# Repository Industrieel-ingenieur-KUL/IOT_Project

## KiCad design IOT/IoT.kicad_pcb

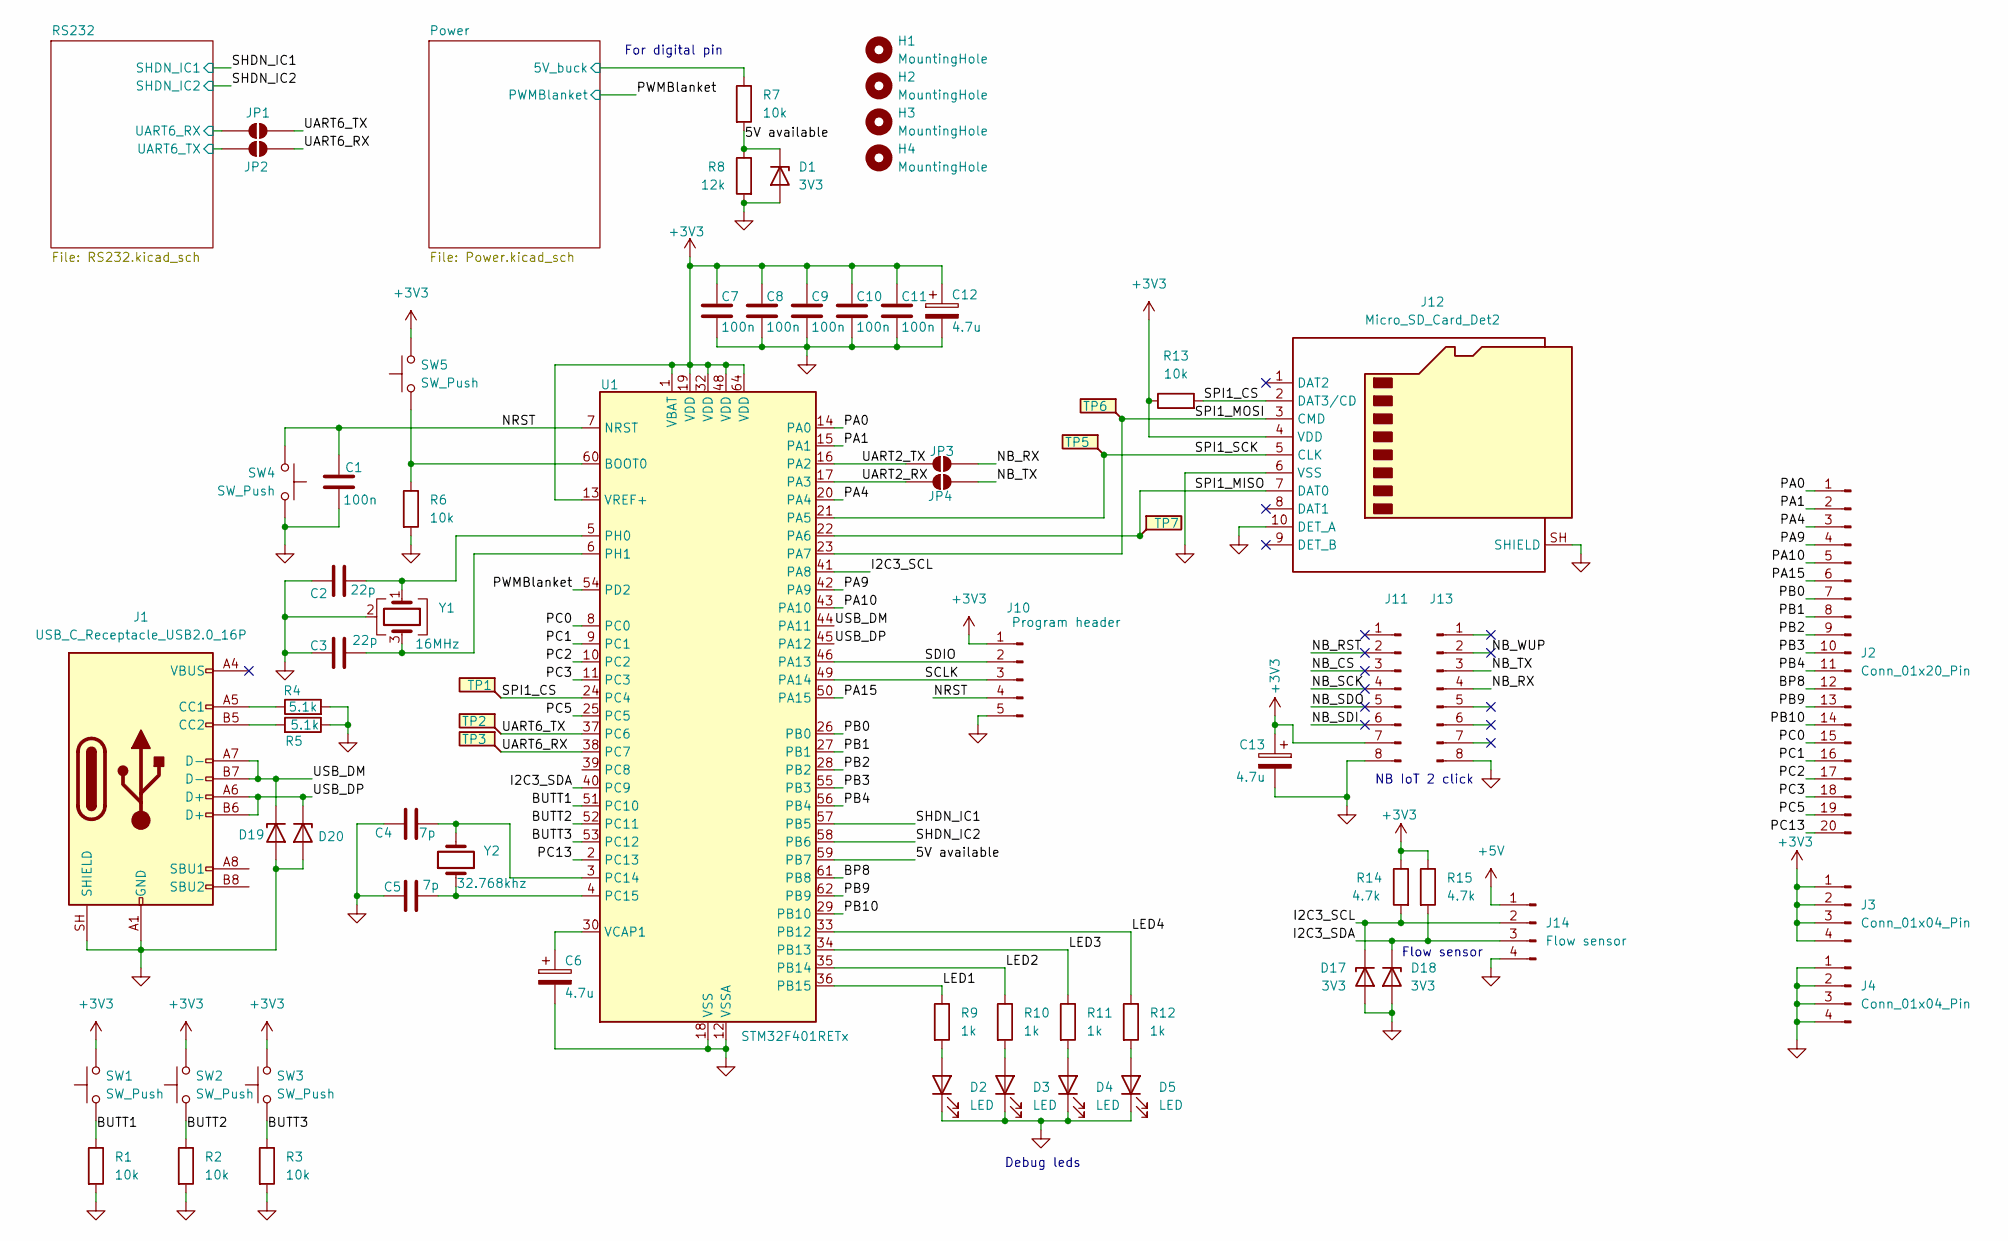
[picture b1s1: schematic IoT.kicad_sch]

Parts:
C1, C7, C8, C9, C10, C11: 100n; C_0805_2012Metric_Pad1.18x1.45mm_HandSolder
C2, C3: 22p; C_0805_2012Metric_Pad1.18x1.45mm_HandSolder
C4, C5: 7p; C_0805_2012Metric_Pad1.18x1.45mm_HandSolder
C6, C12, C13: 4.7u; C_0805_2012Metric_Pad1.18x1.45mm_HandSolder
D1, D17, D18: 3V3; Nexperia_CFP3_SOD-123W
D2, D3, D4, D5: LED; D_0805_2012Metric_Pad1.15x1.40mm_HandSolder
D19, D20: PTVS5V0Z1USK; D_1206_3216Metric_Pad1.42x1.75mm_HandSolder
H1, H2, H3, H4: MountingHole; MountingHole_5.3mm_M5_ISO14580
J1: USB_C_Receptacle_USB2.0_16P; USB_C_Receptacle_G-Switch_GT-USB-7010ASV
J2: Conn_01x20_Pin; PinHeader_1x20_P2.54mm_Vertical
J3, J4: Conn_01x04_Pin; PinSocket_1x04_P2.54mm_Vertical
J10: Program header; PinSocket_1x05_P2.54mm_Vertical
J11, J13: Conn_01x08_Pin; PinSocket_1x08_P2.54mm_Vertical
J12: Micro_SD_Card_Det2; microSD_HC_Molex_104031-0811
J14: Flow sensor; PinSocket_1x04_P2.54mm_Vertical
JP1, JP2, JP3, JP4: SolderJumper_2_Open; SolderJumper-2_P1.3mm_Open_RoundedPad1.0x1.5mm
R1, R2, R3, R6, R7, R13: 10k; LED_1206_3216Metric_Pad1.42x1.75mm_HandSolder
R4, R5: 5.1k; LED_1206_3216Metric_Pad1.42x1.75mm_HandSolder
R8: 12k; LED_1206_3216Metric_Pad1.42x1.75mm_HandSolder
R9, R10, R11, R12: 1k; LED_1206_3216Metric_Pad1.42x1.75mm_HandSolder
R14, R15: 4.7k; LED_1206_3216Metric_Pad1.42x1.75mm_HandSolder
SW1, SW2, SW3, SW4, SW5: SW_Push; SW_DIP_SPSTx01_Slide_6.7x4.1mm_W6.73mm_P2.54mm_LowProfile_J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
TP1, TP2, TP3, TP5, TP6, TP7: TestPoint_Flag; Pin_D0.7mm_L6.5mm_W1.8mm_FlatFork
U1: STM32F401RETx; LQFP-64_10x10mm_P0.5mm
Y1: 16MHz; Crystal_SMD_Abracon_ABM8AIG-4Pin_3.2x2.5mm
Y2: 32.768khz; Crystal_SMD_3215-2Pin_3.2x1.5mm

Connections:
+3V3: C7.1, C8.1, C9.1, C10.1, C11.1, C12.1, C13.1, J3.1, J3.2, J3.3, J3.4, J10.1, J11.7, J12.4 (VDD), R13.1, R14.1, R15.1, SW1.2, SW2.2, SW3.2, SW5.2, U1.1 (VBAT), U1.13 (VREF+), U1.19 (VDD), U1.32 (VDD), U1.48 (VDD), U1.64 (VDD); also elsewhere on the board
+5V: J14.1; also elsewhere on the board
/5V available: D1.1 (K), R7.2, R8.1, U1.59 (PB7)
/BP8: J2.12, U1.61 (PB8)
/BUTT1: R1.1, SW1.1, U1.51 (PC10)
/BUTT2: R2.1, SW2.1, U1.52 (PC11)
/BUTT3: R3.1, SW3.1, U1.53 (PC12)
/I2C3_SCL: D17.1 (K), J14.2, R14.2, U1.41 (PA8)
/I2C3_SDA: D18.1 (K), J14.3, R15.2, U1.40 (PC9)
/LED1: R9.1, U1.36 (PB15)
/LED2: R10.1, U1.35 (PB14)
/LED3: R11.1, U1.34 (PB13)
/LED4: R12.1, U1.33 (PB12)
/NB_CS: J11.3
/NB_RST: J11.2
/NB_RX: J13.4, JP3.2 (B)
/NB_SCK: J11.4
/NB_SDI: J11.6
/NB_SDO: J11.5
/NB_TX: J13.3, JP4.2 (B)
/NB_WUP: J13.2
/NRST: C1.1, J10.4, SW4.2, U1.7 (NRST)
/PA0: J2.1, U1.14 (PA0)
/PA1: J2.2, U1.15 (PA1)
/PA4: J2.3, U1.20 (PA4)
/PA9: J2.4, U1.42 (PA9)
/PA10: J2.5, U1.43 (PA10)
/PA15: J2.6, U1.50 (PA15)
/PB0: J2.7, U1.26 (PB0)
/PB1: J2.8, U1.27 (PB1)
/PB2: J2.9, U1.28 (PB2)
/PB3: J2.10, U1.55 (PB3)
/PB4: J2.11, U1.56 (PB4)
/PB9: J2.13, U1.62 (PB9)
/PB10: J2.14, U1.29 (PB10)
/PC0: J2.15, U1.8 (PC0)
/PC1: J2.16, U1.9 (PC1)
/PC2: J2.17, U1.10 (PC2)
/PC3: J2.18, U1.11 (PC3)
/PC5: J2.19, U1.25 (PC5)
/PC13: J2.20, U1.2 (PC13)
/PWMBlanket: U1.54 (PD2); also elsewhere on the board
/Power/5V_Buck: R7.1; also elsewhere on the board
/RS232/UART6_RX: JP1.1 (A); also elsewhere on the board
/RS232/UART6_TX: JP2.1 (A); also elsewhere on the board
/SCLK: J10.3, U1.49 (PA14)
/SDIO: J10.2, U1.46 (PA13)
/SHDN_IC1: U1.57 (PB5); also elsewhere on the board
/SHDN_IC2: U1.58 (PB6); also elsewhere on the board
/SPI1_CS: J12.2 (DAT3/CD), R13.2, TP1.1 (1_1), U1.24 (PC4)
/SPI1_MISO: J12.7 (DAT0), TP7.1 (1_1), U1.22 (PA6)
/SPI1_MOSI: J12.3 (CMD), TP6.1 (1_1), U1.23 (PA7)
/SPI1_SCK: J12.5 (CLK), TP5.1 (1_1), U1.21 (PA5)
/UART2_RX: JP4.1 (A), U1.17 (PA3)
/UART2_TX: JP3.1 (A), U1.16 (PA2)
/UART6_RX: JP2.2 (B), TP3.1 (1_1), U1.38 (PC7)
/UART6_TX: JP1.2 (B), TP2.1 (1_1), U1.37 (PC6)
/USB_DM: D19.1 (K), J1.A7 (D-), J1.B7 (D-), U1.44 (PA11)
/USB_DP: D20.1 (K), J1.A6 (D+), J1.B6 (D+), U1.45 (PA12)
GND: C1.2, C2.1, C3.1, C4.1, C5.1, C6.2, C7.2, C8.2, C9.2, C10.2, C11.2, C12.2, C13.2, D1.2 (A), D2.1 (K), D3.1 (K), D4.1 (K), D5.1 (K), D17.2 (A), D18.2 (A), D19.2 (A), D20.2 (A), J1.A1 (GND), J1.A12 (GND), J1.B1 (GND), J1.B12 (GND), J1.SH (SHIELD), J4.1, J4.2, J4.3, J4.4, J10.5, J11.8, J12.6 (VSS), J12.10 (DET_A), J12.SH (SHIELD), J13.8, J14.4, R1.2, R2.2, R3.2, R4.2, R5.1, R6.2, R8.2, SW4.1, U1.12 (VSSA), U1.18 (VSS), U1.31 (VSS), U1.47 (VSS), U1.63 (VSS), Y1.2 (G), Y1.4 (G); also elsewhere on the board
unnamed: D2.2 (A), R9.2
unnamed: D3.2 (A), R10.2
unnamed: D4.2 (A), R11.2
unnamed: D5.2 (A), R12.2
unnamed: J1.A5 (CC1), R4.1
unnamed: J1.B5 (CC2), R5.2
unnamed: R6.1, SW5.1, U1.60 (BOOT0)
unnamed: C4.2, U1.3 (PC14), Y2.2
unnamed: C5.2, U1.4 (PC15), Y2.1
unnamed: C2.2, U1.5 (PH0), Y1.1
unnamed: C3.2, U1.6 (PH1), Y1.3
unnamed: C6.1, U1.30 (VCAP1)

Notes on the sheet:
Debug leds
For digital pin
Flow sensor
NB IoT 2 click

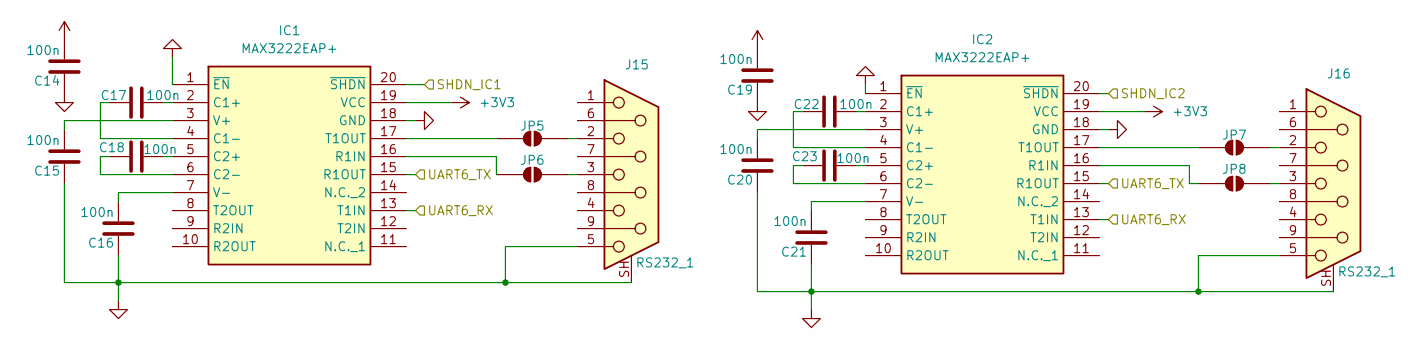
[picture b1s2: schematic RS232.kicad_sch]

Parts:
C14, C15, C16, C17, C18, C19, C20, C21, C22, C23: 100n; C_0805_2012Metric_Pad1.18x1.45mm_HandSolder
IC1, IC2: MAX3222EAP+; TSSOP-20_4.4x5mm_P0.4mm; Mouser Part Number 700-MAX3222EAP
J15, J16: RS232_1; DSUB-9_Pins_Horizontal_P2.77x2.84mm_EdgePinOffset14.56mm_Ho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
JP5, JP6, JP7, JP8: SolderJumper_2_Open; SolderJumper-2_P1.3mm_Open_RoundedPad1.0x1.5mm

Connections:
+3V3: C14.2, C19.2, IC1.19 (VCC), IC2.19 (VCC); also elsewhere on the board
/RS232/UART6_RX: IC1.13 (T1IN), IC2.13 (T1IN); also elsewhere on the board
/RS232/UART6_TX: IC1.15 (R1OUT), IC2.15 (R1OUT); also elsewhere on the board
/SHDN_IC1: IC1.20 (~SHDN); also elsewhere on the board
/SHDN_IC2: IC2.20 (~SHDN); also elsewhere on the board
GND: C14.1, C15.1, C16.1, C19.1, C20.1, C21.1, IC1.1 (~EN), IC1.18 (GND), IC2.1 (~EN), IC2.18 (GND), J15.5, J15.SH (PAD), J16.5, J16.SH (PAD); also elsewhere on the board
unnamed: C17.2, IC1.2 (C1+)
unnamed: C17.1, IC1.4 (C1-)
unnamed: C18.2, IC1.5 (C2+)
unnamed: C18.1, IC1.6 (C2-)
unnamed: IC1.16 (R1IN), JP6.1 (A)
unnamed: IC1.17 (T1OUT), JP5.1 (A)
unnamed: C15.2, IC1.3 (V+)
unnamed: C16.2, IC1.7 (V-)
unnamed: C22.2, IC2.2 (C1+)
unnamed: C22.1, IC2.4 (C1-)
unnamed: C23.2, IC2.5 (C2+)
unnamed: C23.1, IC2.6 (C2-)
unnamed: IC2.16 (R1IN), JP8.1 (A)
unnamed: IC2.17 (T1OUT), JP7.1 (A)
unnamed: C20.2, IC2.3 (V+)
unnamed: C21.2, IC2.7 (V-)
unnamed: J15.2, JP5.2 (B)
unnamed: J15.3, JP6.2 (B)
unnamed: J16.2, JP7.2 (B)
unnamed: J16.3, JP8.2 (B)

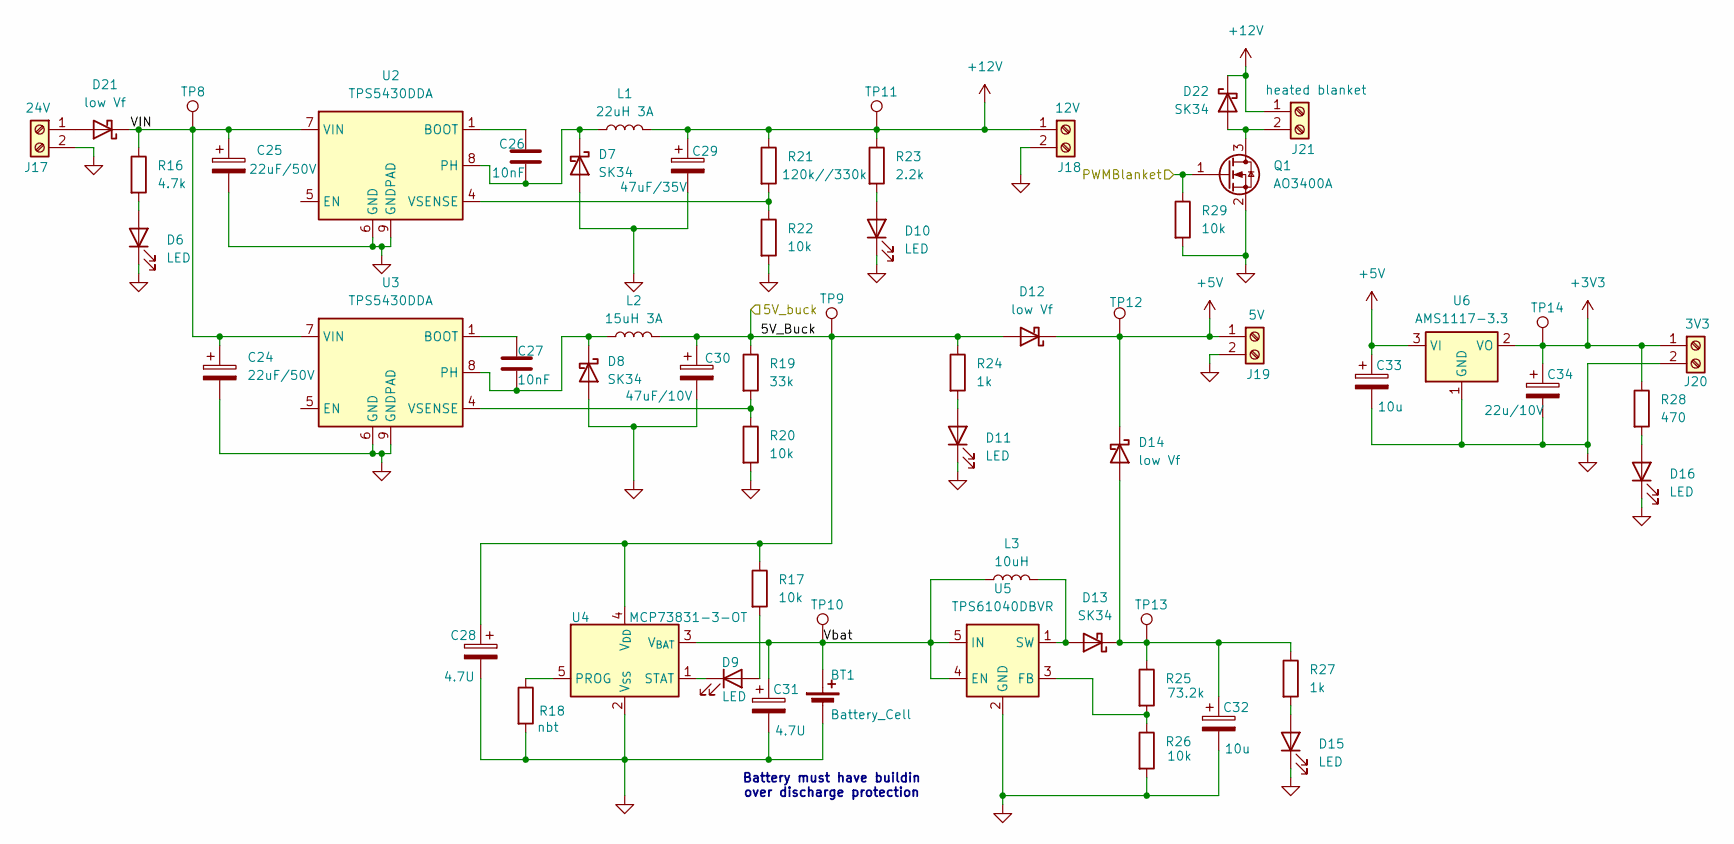
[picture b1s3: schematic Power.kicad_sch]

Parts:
BT1: Battery_Cell; BatteryHolder_MPD_BH-18650-PC
C24, C25: 22uF/50V; CP_Elec_5x5.4
C26, C27: 10nF; C_0805_2012Metric_Pad1.18x1.45mm_HandSolder
C28, C31: 4.7U; CP_Elec_4x5.4
C29: 47uF/35V; CP_Elec_8x10
C30: 47uF/10V; CP_Elec_8x10
C32, C33: 10u; C_0805_2012Metric_Pad1.18x1.45mm_HandSolder
C34: 22u/10V; CP_EIA-3528-12_Kemet-T_HandSolder
D6, D9, D10, D11, D15, D16: LED; D_0805_2012Metric_Pad1.15x1.40mm_HandSolder
D7, D8, D13, D22: SK34; D_SMA_Handsoldering
D12, D14, D21: low Vf; D_SMC_Handsoldering
J17: 24V; TerminalBlock_Philmore_TB132_1x02_P5.00mm_Horizontal
J18: 12V; TerminalBlock_Philmore_TB132_1x02_P5.00mm_Horizontal
J19: 5V; TerminalBlock_Philmore_TB132_1x02_P5.00mm_Horizontal
J20: 3V3; TerminalBlock_Philmore_TB132_1x02_P5.00mm_Horizontal
J21: heated blanket; TerminalBlock_Philmore_TB132_1x02_P5.00mm_Horizontal
L1: 22uH 3A; L_Wuerth_WE-PD-Typ-LS_Handsoldering
L2: 15uH 3A; L_Bourns_SRP7028A_7.3x6.6mm
L3: 10uH; L_Bourns_SRP7028A_7.3x6.6mm
Q1: AO3400A; SOT-23
R16: 4.7k; LED_1206_3216Metric_Pad1.42x1.75mm_HandSolder
R17, R20, R22, R26, R29: 10k; LED_1206_3216Metric_Pad1.42x1.75mm_HandSolder
R18: nbt; LED_1206_3216Metric_Pad1.42x1.75mm_HandSolder
R19: 33k; LED_1206_3216Metric_Pad1.42x1.75mm_HandSolder
R21: 120k//330k; LED_1206_3216Metric_Pad1.42x1.75mm_HandSolder
R23: 2.2k; LED_1206_3216Metric_Pad1.42x1.75mm_HandSolder
R24, R27: 1k; LED_1206_3216Metric_Pad1.42x1.75mm_HandSolder
R25: 73.2k; LED_1206_3216Metric_Pad1.42x1.75mm_HandSolder
R28: 470; LED_1206_3216Metric_Pad1.42x1.75mm_HandSolder
TP8, TP9, TP10, TP11, TP12, TP13, TP14: TestPoint; Pin_D0.7mm_L6.5mm_W1.8mm_FlatFork
U2, U3: TPS5430DDA; TI_SO-PowerPAD-8_ThermalVias
U4: MCP73831-3-OT; SOT-23-5
U5: TPS61040DBVR; SOT-23-6
U6: AMS1117-3.3; SOT-223-3_TabPin2

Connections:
+3V3: C34.1, J20.1, R28.1, TP14.1 (1_1), U6.2 (VO); also elsewhere on the board
+5V: C33.1, D12.1 (K), D14.1 (K), J19.1, TP12.1 (1_1), U6.3 (VI); also elsewhere on the board
+12V: C29.1, D22.1 (K), J18.1, J21.1, L1.2, R21.1, R23.1, TP11.1 (1_1)
/PWMBlanket: Q1.1 (G), R29.1; also elsewhere on the board
/Power/5V_Buck: C28.1, C30.1, D12.2 (A), L2.2, R17.1, R19.1, R24.1, TP9.1 (1_1), U4.4 (V_{DD}); also elsewhere on the board
/Power/VIN: C24.1, C25.1, D21.1 (K), R16.1, TP8.1 (1_1), U2.7 (VIN), U3.7 (VIN)
/Power/Vbat: BT1.1 (+), C31.1, L3.1, TP10.1 (1_1), U4.3 (V_{BAT}), U5.4 (EN), U5.5 (IN)
GND: BT1.2 (-), C24.2, C25.2, C28.2, C29.2, C30.2, C31.2, C32.2, C33.2, C34.2, D6.1 (K), D7.2 (A), D8.2 (A), D10.1 (K), D11.1 (K), D15.1 (K), D16.1 (K), J17.2, J18.2, J19.2, J20.2, Q1.2 (S), R18.2, R20.2, R22.2, R26.2, R29.2, U2.6 (GND), U2.9 (GNDPAD), U3.6 (GND), U3.9 (GNDPAD), U4.2 (V_{SS}), U5.2 (GND), U6.1 (GND); also elsewhere on the board
unnamed: D6.2 (A), R16.2
unnamed: C26.2, D7.1 (K), L1.1, U2.8 (PH)
unnamed: C27.2, D8.1 (K), L2.1, U3.8 (PH)
unnamed: D9.2 (A), R17.2
unnamed: D9.1 (K), U4.1 (STAT)
unnamed: D10.2 (A), R23.2
unnamed: D11.2 (A), R24.2
unnamed: D13.2 (A), L3.2, U5.1 (SW)
unnamed: C32.1, D13.1 (K), D14.2 (A), R25.1, R27.1, TP13.1 (1_1)
unnamed: D15.2 (A), R27.2
unnamed: D16.2 (A), R28.2
unnamed: D21.2 (A), J17.1
unnamed: D22.2 (A), J21.2, Q1.3 (D)
unnamed: C26.1, U2.1 (BOOT)
unnamed: R21.2, R22.1, U2.4 (VSENSE)
unnamed: C27.1, U3.1 (BOOT)
unnamed: R19.2, R20.1, U3.4 (VSENSE)
unnamed: R18.1, U4.5 (PROG)
unnamed: R25.2, R26.1, U5.3 (FB)

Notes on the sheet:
Battery must have buildin over discharge protection

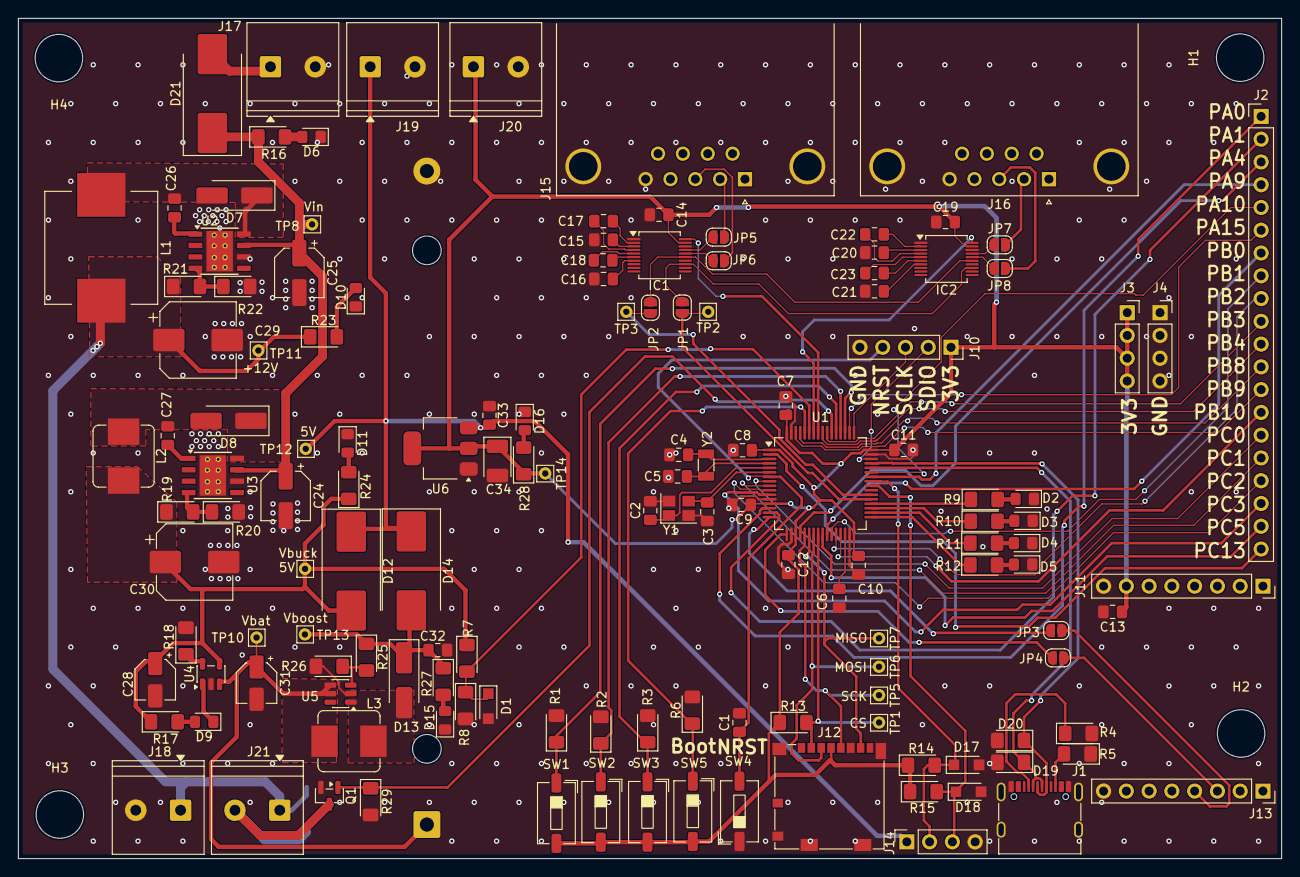
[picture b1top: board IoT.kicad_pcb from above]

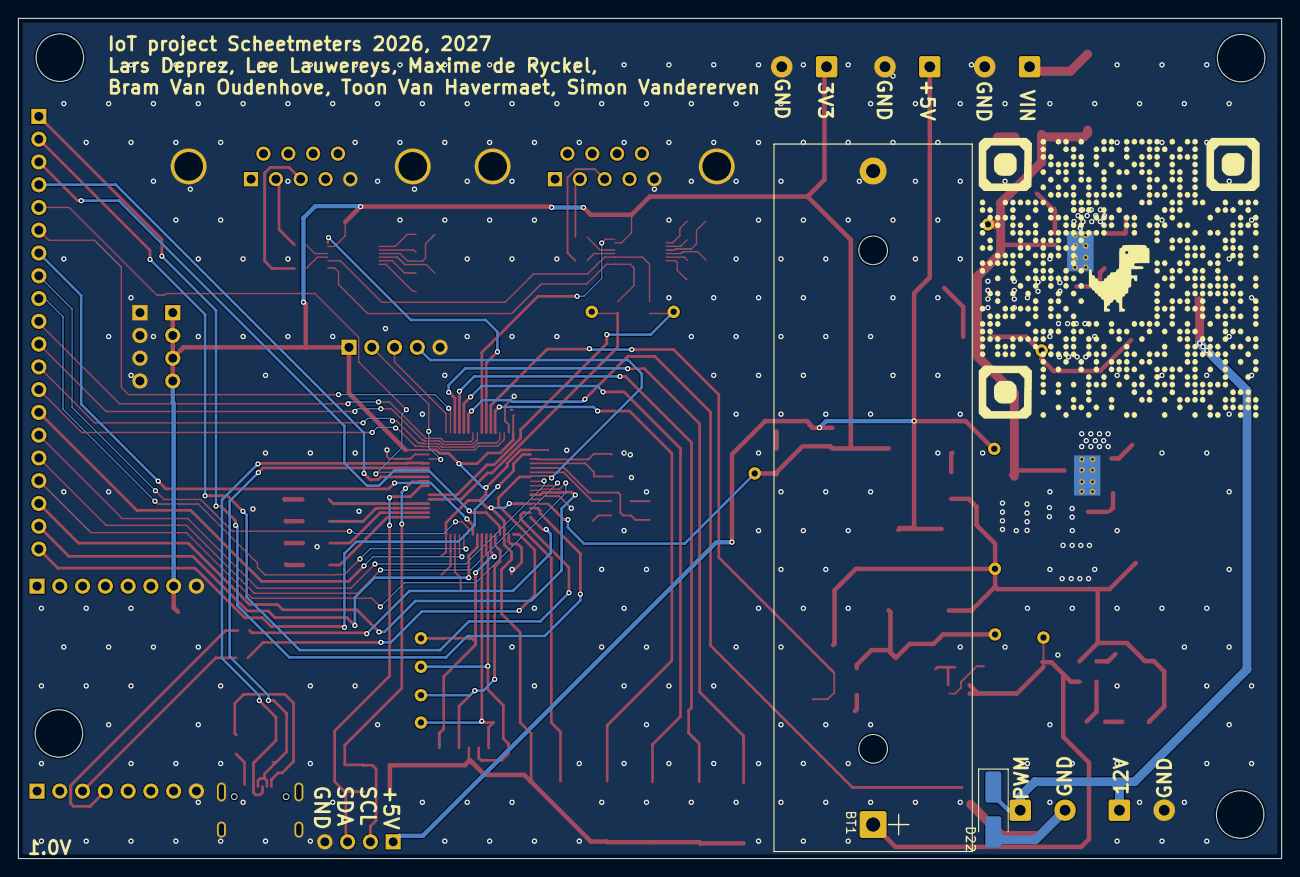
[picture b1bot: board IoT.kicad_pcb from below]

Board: 2 copper layers, 140.9 x 93.7 mm, 146 parts (2 on the bottom side), 108 nets.

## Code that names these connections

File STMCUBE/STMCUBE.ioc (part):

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Mcu.Name=STM32F401R(D-E)Tx
Mcu.Package=LQFP64
Mcu.UserName=STM32F401RETx
PA11.Mode=Device_Only
PA11.Signal=USB_OTG_FS_DM
PA12.Mode=Device_Only
PA12.Signal=USB_OTG_FS_DP
PA13.Signal=SYS_JTMS-SWDIO
PA14.Signal=SYS_JTCK-SWCLK
PA2.Mode=Asynchronous
PA2.Signal=USART2_TX
PA3.Mode=Asynchronous
PA3.Signal=USART2_RX
PA5.Mode=Full_Duplex_Master
PA5.Signal=SPI1_SCK
PA6.Mode=Full_Duplex_Master
PA6.Signal=SPI1_MISO
PA7.Mode=Full_Duplex_Master
PA7.Signal=SPI1_MOSI
PA8.Mode=I2C
PA8.Signal=I2C3_SCL
PB12.GPIOParameters=GPIO_Label
PB12.GPIO_Label=LED4
PB12.Signal=GPIO_Output
PB13.GPIOParameters=GPIO_Label
PB13.GPIO_Label=LED3
PB13.Signal=GPIO_Output
PB14.GPIOParameters=GPIO_Label
PB14.GPIO_Label=LED2
PB14.Signal=GPIO_Output
PB5.GPIOParameters=GPIO_Label
PB5.GPIO_Label=SHDN_IC1
PB5.Signal=GPIO_Output
PB6.GPIOParameters=GPIO_Label
PB6.GPIO_Label=SHDN_IC2
PB6.Signal=GPIO_Output
PB7.GPIOParameters=GPIO_Label
PB7.GPIO_Label=V5V_available
PB7.Signal=GPIO_Input
PC10.GPIOParameters=GPIO_Label
PC10.GPIO_Label=BP1
PC10.Signal=GPIO_Input
PC11.GPIOParameters=GPIO_Label
PC11.GPIO_Label=PB2
PC11.Signal=GPIO_Input
PC12.GPIOParameters=GPIO_Label
PC12.GPIO_Label=PB3
PC12.Signal=GPIO_Input
PC14-OSC32_IN.Signal=RCC_OSC32_IN
PC15-OSC32_OUT.Signal=RCC_OSC32_OUT
PC4.GPIOParameters=GPIO_Label
PC4.GPIO_Label=SPI1_CS
PC4.Signal=GPIO_Output
PC6.Mode=Asynchronous
PC6.Signal=USART6_TX
PC7.Mode=Asynchronous
PC7.Signal=USART6_RX
PC8.GPIOParameters=GPIO_Label
PC8.GPIO_Label=LED1
PC8.Signal=GPIO_Output
PC9.Mode=I2C
PC9.Signal=I2C3_SDA
PH0\ -\ OSC_IN.Signal=RCC_OSC_IN
PH1\ -\ OSC_OUT.Signal=RCC_OSC_OUT
RCC.HSE_VALUE=25000000
RCC.SYSCLKFreq_VALUE=16000000
board=custom
